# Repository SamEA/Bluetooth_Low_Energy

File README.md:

HM-10 Breakout Board
====================

<br />

The HM-10 breakout board provides breadboard-pitch access to the HM-10 BLE module. 
The HM-10's on board TI CC2540 is fully programmable with CC-Debugger or SmartRF04EB.

##Bill of Materials

If you are planning on ordering the PCB through OSHPark, you should note that you will receive three copies of the board. You may want to go ahead and order three of each component you intend to use. Digi-Key numbers are provided as a courtesy; check ebay or any other preferred supplier for better pricing. As long as the component matches the packaging a specifications, it should be fine.

At a bare minimum, the PCB, HM-10 module, reset switch, the 1uF capacitor, and one 1kΩ resistor are required. Indicator LEDs are optional, as are the accompanying 470Ω resistors. Additionally, the CC debugger header and and USB connector are optional; if you elect to leave this off you may also leave off the two 33Ω resistors, the 1.5kΩ resistor and the fuse. The 3.3v regulator is only available to be populated if you want to use the USB connector (which is at 5v). Using it in other situations defeats the purpose of using a low power communications technology. If you are leaving off the regulator, you may also leave off the .47uF and 2.2uF capacitors.

Part (Digi-Key #) | Quantity | Optional (Required For)
:---------------- | :-------:| :----------------------
[Breakout PCB](https://oshpark.com/shared_projects/mgt9vH1j)  | 1 | No
[HM-10 Module](http://www.fasttech.com/products/0/10004051/1292002-ti-cc2540-bluetooth-40-ble-2540-transparent-serial) | 1 | No
[0603 1uF Capacitor](http://www.digikey.com/product-detail/en/CC0603ZRY5V7BB105/311-1372-1-ND/2103156) (311-1372-1-ND) | 1 | No
[Tactile Switch](http://www.digikey.com/product-detail/en/PTS645SH50SMTR92%20LFS/CKN9085CT-ND/1146817) (CKN9085CT-ND) | 1 | No
[0603 1kΩ Resistor](http://www.digikey.com/product-detail/en/RC0603JR-071KL/311-1.0KGRCT-ND/729624) (311-1.0KGRCT-ND) | 1 | No
[CC Debugger Header](http://www.digikey.com/product-detail/en/20021121-00010C4LF/609-3695-1-ND/2209147) (609-3695-1-ND)  | 1 | Yes (CC Debug capability)
[0603 LED](http://www.digikey.com/product-detail/en/LTST-C191KRKT/160-1447-1-ND/386836) (160-1447-1-ND) | 1 | Yes (LEDs)
[0603 LED (>3v drop)](http://www.digikey.com/product-detail/en/APT1608QBC%2FD/754-1434-1-ND/2163792) (754-1434-1-ND) | 2 | Yes (LEDs)
[0603 470Ω Resistor](http://www.digikey.com/product-detail/en/RC0603JR-07470RL/311-470GRCT-ND/729738) (311-470GRCT-ND)| 2 | Yes (LEDs)
[Micro USB Connector](http://www.digikey.com/product-detail/en/0475890001/WM17143TR-ND/1832253) (WM17143TR-ND) | 1 | Yes (USB)
[0603 33Ω Resistor](http://www.digikey.com/product-detail/en/RC0603JR-0733RL/311-33GRCT-ND/729718) (311-33GRCT-ND) | 2 | Yes (USB)
[0603 1.5kΩ Resistor](http://www.digikey.com/product-detail/en/RMCF0603FT1K50/RMCF0603FT1K50CT-ND/1943003) (RMCF0603FT1K50CT-ND) | 1 | Yes (USB)
[0603 Fuse](http://www.digikey.com/product-detail/en/0603SFF400F%2F32-2/0603SFF400F%2F32CT-ND/686744) (0603SFF400F/32CT-ND) | 1 | Yes (USB)
[SOT-23 MCP1700 Voltage Regulator](http://www.digikey.com/product-detail/en/MCP1700T-3302E%2FTT/MCP1700T3302ETTCT-ND/652677) (MCP1700T3302ETTCT-ND) | 1 | Yes (USB; 5v external power)
[0603 .47uF Capacitor](http://www.digikey.com/product-detail/en/C0603C474J4RACTU/399-7339-1-ND/3316954) (399-7339-1-ND) | 1 | Yes (3.3v regulator)
[0603 2.2uF Capacitor](http://www.digikey.com/product-detail/en/GRM188R61A225KE34D/490-1545-1-ND/587767) (490-1545-1-ND) | 2 | Yes (3.3v regulator)  

##Links

Assembly: http://www.instructables.com/id/How-to-Create-an-Arduino-Compatible-Bluetooth-40-M/

On-going HM-10 research: http://letsmakerobots.com/node/38009

Info about the HM-10 module: http://www.jnhuamao.cn/

HM-10 Datasheet:  http://www.jnhuamao.cn/bluetooth40_en.rar

Info about the famous CC2540: http://www.ti.com/product/cc2540&DCMP=LowPowerRFICs+Other&HQS=Other+OT+cc2540

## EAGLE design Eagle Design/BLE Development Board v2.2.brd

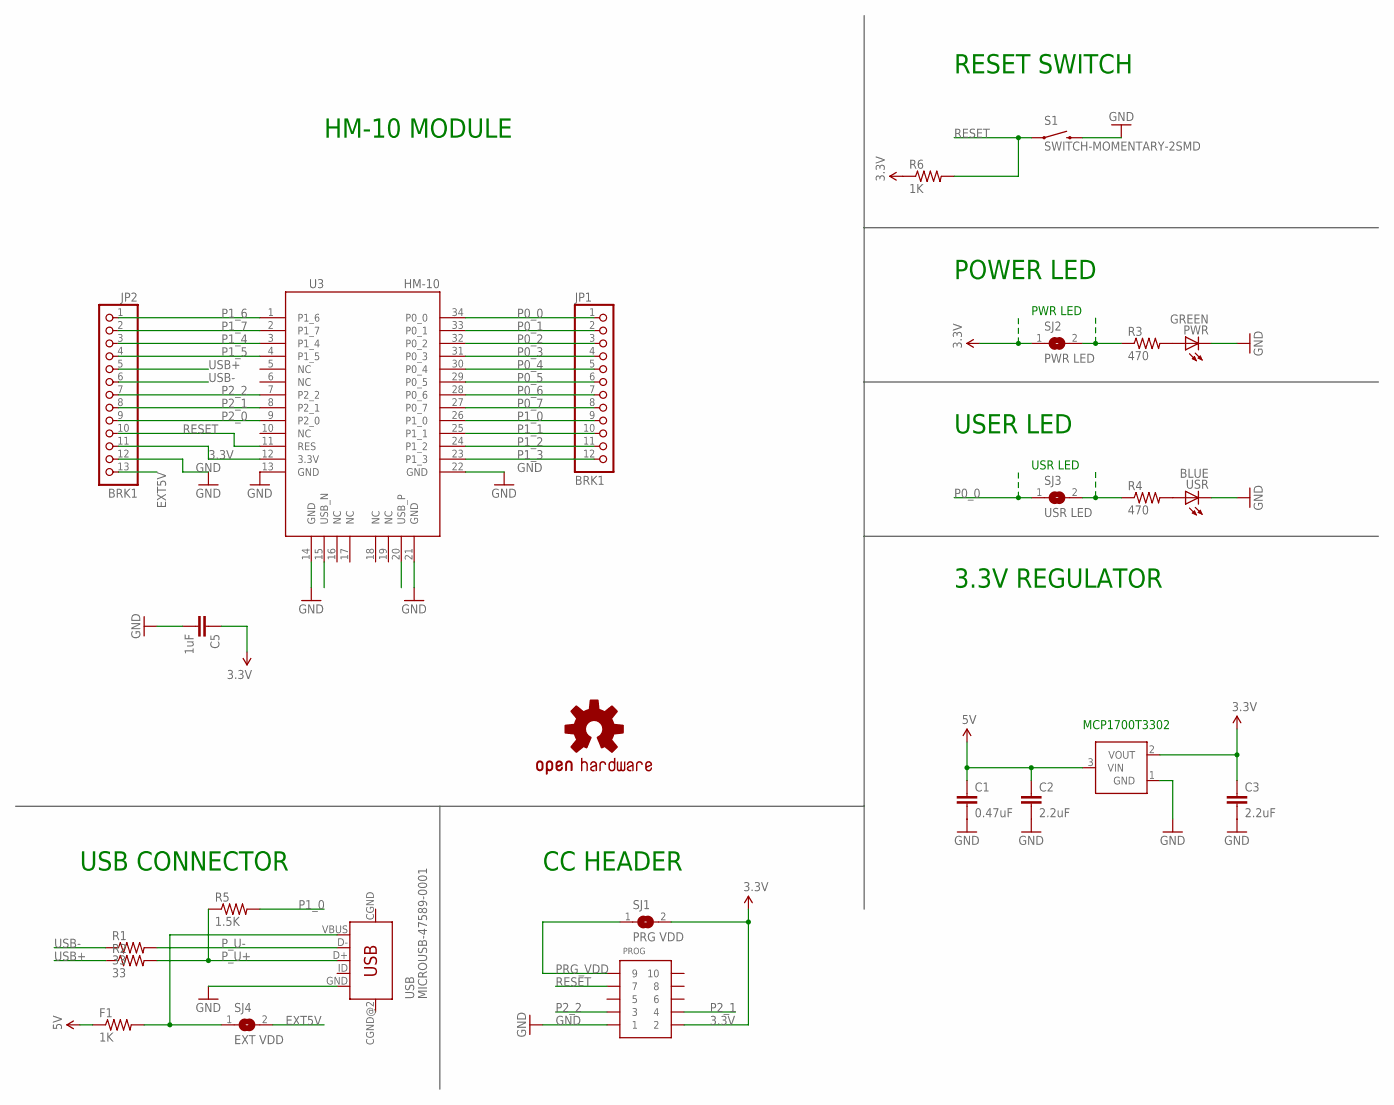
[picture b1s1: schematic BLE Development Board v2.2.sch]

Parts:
C1: 0.47uF; 0603-CAP
C2, C3: 2.2uF; 0603-CAP
C5: 1uF; 0603-CAP
F1: 1K; 0805
JP1: BRK1; 1X12
JP2: BRK1; 1X13
OSHW1: OSHW-LOGOL; OSHW-LOGO-L
PROG: CONN_5-2-FTSH-V; FTSH-105-DV
PWR: GREEN; CHIPLED_0603
R1, R2: 33; 0603-RES
R3, R4: 470; R0603
R5: 1.5K; 0603-RES
R6: 1K; R0603
S1: SWITCH-MOMENTARY-2SMD; TACTILE_SWITCH_SMD
SJ1: PRG VDD; SJ
SJ2: PWR LED; SJ
SJ3: USR LED; SJ
SJ4: EXT VDD; SJ
U2: MCP1700; SOT23-3
U3: HM-10
USB: MICROUSB-47589-0001
USR: BLUE; CHIPLED_0603

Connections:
3.3V: C3.1, C5.1, JP2.11, PROG.2, R6.1, SJ1.2, SJ2.1, U2.2 (VOUT), U3.12 (3.3V)
5V: C1.1, C2.1, F1.1, U2.3 (VIN)
EXT5V: JP2.13, SJ4.2
GND: C1.2, C2.2, C3.2, C5.2, JP2.12, PROG.1, PWR.C, S1.3 (2), U2.1 (GND), U3.13 (GND), U3.14 (GND), U3.21 (GND), U3.22 (GND), USB.GND, USR.C
unnamed: PWR.A, R3.2
unnamed: R3.1, SJ2.2
unnamed: R4.2, USR.A
unnamed: R4.1, SJ3.2
P0_0: JP1.1, SJ3.1, U3.34 (P0_0)
P0_1: JP1.2, U3.33 (P0_1)
P0_2: JP1.3, U3.32 (P0_2)
P0_3: JP1.4, U3.31 (P0_3)
P0_4: JP1.5, U3.30 (P0_4)
P0_5: JP1.6, U3.29 (P0_5)
P0_6: JP1.7, U3.28 (P0_6)
P0_7: JP1.8, U3.27 (P0_7)
P1_0: JP1.9, R5.2, U3.26 (P1_0)
P1_1: JP1.10, U3.25 (P1_1)
P1_2: JP1.11, U3.24 (P1_2)
P1_3: JP1.12, U3.23 (P1_3)
P1_4: JP2.3, U3.3 (P1_4)
P1_5: JP2.4, U3.4 (P1_5)
P1_6: JP2.1, U3.1 (P1_6)
P1_7: JP2.2, U3.2 (P1_7)
P2_0: JP2.9, U3.9 (P2_0)
P2_1: JP2.8, PROG.4, U3.8 (P2_1)
P2_2: JP2.7, PROG.3, U3.7 (P2_2)
PRG_VDD: PROG.9, SJ1.1
P_U+: R2.2, R5.1, USB.D+
P_U-: R1.2, USB.D-
RESET: JP2.10, PROG.7, R6.2, S1.1, U3.11 (RES)
USB+: JP2.5, R2.1, U3.20 (USB_P)
USB-: JP2.6, R1.1, U3.15 (USB_N)
VBUS: F1.2, SJ4.1, USB.VBUS

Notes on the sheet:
PWR LED
USR LED
POWER LED
USER LED
USB CONNECTOR
CC HEADER
HM-10 MODULE
3.3V REGULATOR
RESET SWITCH
MCP1700T3302

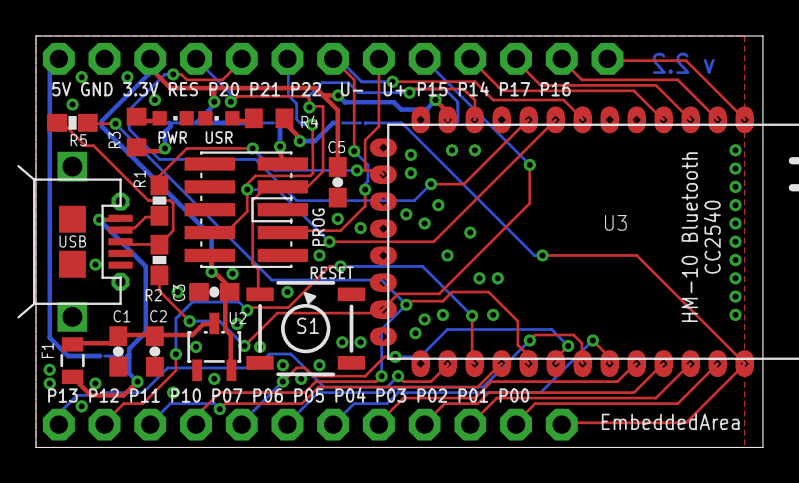
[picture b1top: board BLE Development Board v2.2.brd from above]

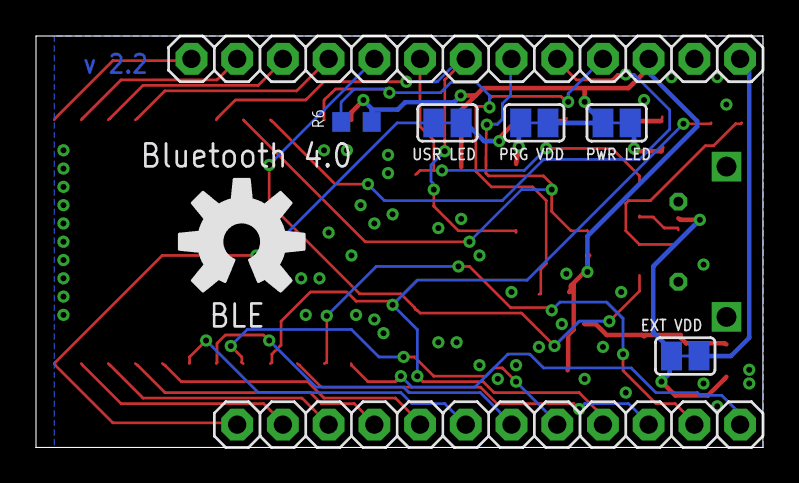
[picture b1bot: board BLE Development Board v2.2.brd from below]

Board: 2 copper layers, 40.4 x 22.9 mm, 25 parts (8 on the bottom side), 34 nets.

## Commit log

2013-10-03 Added Images
2013-10-03 Added Library
    HM-10 Library for Eagle
2013-10-03 New Development Board
2013-10-06 improved version
2013-10-10 Fixed Power/Reset issue.
    Fixed Power and Reset issue. Added a pull-up resistor on reset pin.
2013-10-10 render of v2.2
2014-04-13 Update readme with BoM, more organization
    Rename images so they can be embedded in the readme
2014-04-13 Change positioning and size of images
2014-04-14 Update BoM
    Add fuse/remove extra 1k resistor

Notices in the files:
parts and their libraries:
SparkFun: Licensing: CC v3.0 Share-Alike You are welcome to use this library for commercial purposes.
